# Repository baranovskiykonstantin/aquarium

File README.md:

# DIY Aquarium Controller

## Features
* The controller is based on ATMEL's microcontroller ATMEGA8A
    * Settings are stored in EEPROM
    * Detecting a system hang with Watchdog.
* Remote control via Bluetooth
    * HC-05 module
    * RFCOMM protocol
    * Baud rate 9600 bps
* LED lighting
    * 12V DC output
    * 400mA max.
    * Adjustable brightness
    * Adjustable gradual turning on/off (0-30 min)
    * Adjustable time of turning on/off the light
* Thermostat
    * 220V AC output
    * 3A max. (fused)
    * Adjustable the min. and max. temperature thresholds
* Water temperature measurement
    * DS18B20 sensor
    * Accuracy 0.5 °C
    * Error detecting
* On-board RTC
    * DS1302 chip
    * Adjustable date&time
    * Adjustable daily time correction
    * Backup battery
* 4-digits LED display
    * Two modes of displaying: the current time or the temperature of the water
* Touch control
    * Touch Sensor 1 to switch displaying mode (time -> temperature -> time -> ...)
    * Touch Sensor 1 and Sensor 2 at the same time to switch the operation mode (on -> off -> auto -> on -> ...) of:
        * the lighting if the display shows the time;
        * the heater if the display shows the temperature;
* [Aquarium-control app](https://github.com/baranovskiykonstantin/aquarium-control) is designed to setup the aquarium settings (Windows, Linux, Android, [Symbian](https://github.com/baranovskiykonstantin/AquariumControlS60))

## Wiring diagram

1. Capacitive sensors (aluminum scotch 10x50mm on inner side of the top cover)
2. Mains plug
3. Aquarium controller PCB
4. Power supply PCB
5. Bluetooth module HC-05
6. LEDs (4 x 1W = 12V 300mA)
7. Waterproof DS18B20
8. Heater

## HC-05 configuration
* Change the indicating mode
   * By default LED is blinking on idle and lighting on connecting
   * Disconnect output LED2(31) from PCB's pad that is going to the LED and connect this pad to LED1(32) output
   * Now LED is not lighting on idle and lighting on connecting
* Restore default settings
   * Enter to AT-command mode
   * Send command `AT+ORGL`
* Set device name
   * Enter to AT-command mode
   * Send command `AT+NAME=aquarium` (the device's name must begin with "aquarium" to be recognized by aquarium-control app)
* Reduce power consumption (from ~40mA to ~3mA on idle!)
   * Enter to AT-command mode
   * Send command `AT+IPSCAN=1024,1,1024,1`

## Communicating with the controller
After establishing a connection, you can send commands to the aquarium
controller to setup it.<br>
If a command has the correct format and can be successfully completed the
controller will send OK response. If the command has the wrong format, the
controller will send ERROR response. If the controller receives an unknown
command it will send UNKNOWN response.<br>
The command must end with `\n` or `\r`. If the value of a parameter is bigger
than allowed one it will be reduced to max. allowed value.

### Command `status`
Get information about current state of the aquarium.

Format:

`status`

Response:

```
Date: 01.01.17 Friday
Time: 13:29:59 (-3 sec at 12:00:00)
Temp: 22
Heat: OFF auto (20-22)
Light: ON manual (10:00:00-20:00:00) 43/50% 10min
Display: time
```

Meaning:

Line 1: the current date and the day of the week;<br>
Line 2: the current time and the information about the daily time correction;<br>
Line 3: the temperature of the water (°C);<br>
Line 4: the thermostat status:<br>
* `ON` - the heater is on, `OFF` - the heater is off
* `auto` - automatic mode, `manual` - manual mode
* the value in the parentheses indicates the temperature range that maintains in the automatic mode<br>

Line 5: the lighting status:<br>
* `ON` - the light is on, `OFF` - the light is off
* `auto` - automatic mode, `manual` - manual mode
* the value in the parentheses indicates the period of time when the light is on in the automatic mode<br>
* at the end, the current/target brightness level in percent and the light rising time in minutes

Line 6: the display mode (`time` - the current time is shown, `temp` - the temperature of the water is shown)

### Command `date`
Set a date.

Format:

`date DD.MN.YY W`

Parameters:<br>
* `DD` - day of the month (01-31)
* `MN` - month (01-12)
* `YY` - year (00-99)
* `W` - day of the week (1 - Monday ... 7 - Sunday)

Response:

`OK` or `ERROR`

### Command `time`
Set a time and/or a time correction

Format 1:

`time HH:MM:SS`

Parameters:<br>
* `HH` - hours (00-23)
* `MM` - minutes (00-59)
* `SS` - seconds (00-59)

Format 2:

`time +CC`<br>
`time -CC`

Parameters:<br>
* `+` or `-` - add or subtract the time correction value
* `CC` - time correction in seconds (00-59)

Format 3:

`time HH:MM:SS +CC`<br>
`time HH:MM:SS -CC`

Parameters:<br>
* `HH` - hours (00-23)
* `MM` - minutes (00-59)
* `SS` - seconds (00-59)
* `+` or `-` - add or subtract the time correction value
* `CC` - time correction in seconds (00-59)

Response:

`OK` or `ERROR`

### Command `heat`
Heater setup.

Format 1:

`heat LO-HI`

Parameters:<br>
* `LO` - minimal temperature (18-35)
* `HI` - maximal temperature (18-35)

Format 2:

`heat on`<br>
`heat off`<br>
`heat auto`<br>

Parameters:<br>
* `on` - switch to the manual mode and turn on heater
* `off` - switch to the manual mode and turn off heater
* `auto` - switch to the automatic mode

Response:

`OK` or `ERROR`

### Command `light`
Lighting setup.

Format 1:

`light H1:M1:S1-H2:M2:S2`

Parameters:<br>
* `H1:M1:S1` - light on time (00:00:00-23:59:59)
* `H2:M2:S2` - light off time (00:00:00-23:59:59)

Format 2:

`light on`<br>
`light off`<br>
`light auto`<br>

Parameters:<br>
* `on` - switch to the manual mode and turn on light
* `off` - switch to the manual mode and turn off light
* `auto` - switch to the automatic mode

Format 3:

`light level LLL`

Parameters:<br>
* `LLL` - brightness level in percent (000-100)

Format: 4:

`light rise RR`

Parameters:<br>
* `RR` - time of the light rising in minutes (00-30)

Format: 5:

`light H1:M1:S1-H2:M2:S2 LLL RR`

Parameters:<br>
* `H1:M1:S1` - time of turn on light (00:00:00-23:59:59)
* `H2:M2:S2` - time of turn off light (00:00:00-23:59:59)
* `LLL` - brightness level (000-100)
* `RR` - light rising time (00-30)

Response:

`OK` or `ERROR`

### Command `display`
Display setup.

Format:

`display time`<br>
`display temp`

Parameters:<br>
* `time` - show the current time
* `temp` - show the current temperature of the water

Response:

`OK` or `ERROR`

### Command `reboot`
Restart the program.

Format:

`reboot`

Response:

`OK`

### Command `help`
Print the list of available commands.

Format:

`help`

Response:

```
Available commands:

status
date DD.MN.YY W
time HH:MM:SS
time +CC
time -CC
time HH:MM:SS +CC
time HH:MM:SS -CC
heat LO-HI
heat on
heat off
heat auto
light H1:M1:S1-H2:M2:S2
light level LLL
light rise RR
light H1:M1:S1-H2:M2:S2 LLL RR
light on
light off
light auto
display time
display temp
reboot
help

```

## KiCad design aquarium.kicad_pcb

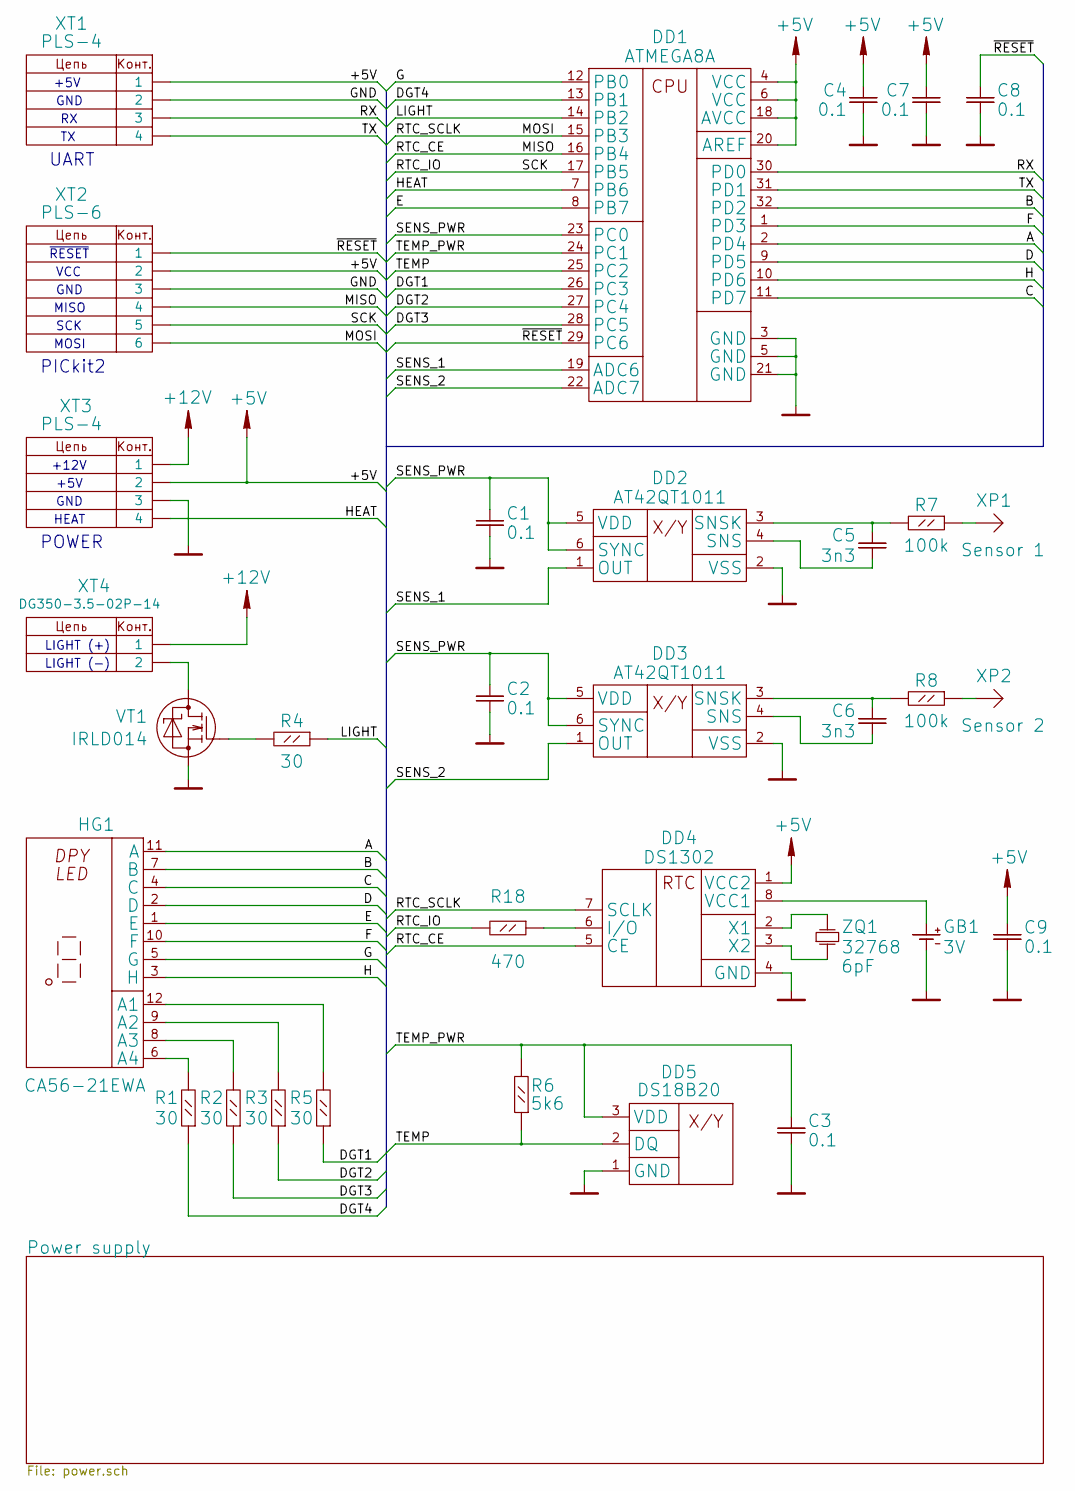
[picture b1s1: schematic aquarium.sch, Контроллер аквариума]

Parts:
C1, C2, C3, C4, C7, C8, C9: 0.1; SMD_0805
C5, C6: 3n3; SMD_0805
DD1: ATMEGA8A; TQFP32-30
DD2, DD3: AT42QT1011; SOT23-6
DD4: DS1302; DIP8-300
DD5: DS18B20; PLS-3
GB1: 3V; CR2032_H
HG1: CA56-21EWA; 56-21_smd
R1, R2, R3, R4, R5: 30; R_0805
R6: 5k6; R_0805
R7, R8: 100k; R_0805
R18: 470; R_0805
VT1: IRLD014; HVMDIP
XP1: Sensor 1; PLS-1
XP2: Sensor 2; PLS-1
XT1, XT3: PLS-4
XT2: PLS-6
XT4: DG350-3.5-02P-14; DG-350-2
ZQ1: 32768; HC_3.0x8.0mm

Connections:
+5V: C4.1, C7.1, C9.1, DD1.4 (VCC), DD1.6 (VCC), DD1.18 (AVCC), DD1.20 (AREF), DD4.1 (VCC2), XT1.1, XT2.2, XT3.2; also elsewhere on the board
+12V: XT3.1, XT4.1; also elsewhere on the board
/A: DD1.2 (PD4), HG1.11 (A)
/B: DD1.32 (PD2), HG1.7 (B)
/C: DD1.11 (PD7), HG1.4 (C)
/D: DD1.9 (PD5), HG1.2 (D)
/DGT1: DD1.26 (PC3), R5.1
/DGT2: DD1.27 (PC4), R3.1
/DGT3: DD1.28 (PC5), R2.1
/DGT4: DD1.13 (PB1), R1.1
/E: DD1.8 (PB7), HG1.1 (E)
/F: DD1.1 (PD3), HG1.10 (F)
/G: DD1.12 (PB0), HG1.5 (G)
/H: DD1.10 (PD6), HG1.3 (H)
/HEAT: DD1.7 (PB6), XT3.4
/LIGHT: DD1.14 (PB2), R4.1
/MISO: DD1.16 (PB4), DD4.5 (CE), XT2.4
/MOSI: DD1.15 (PB3), DD4.7 (SCLK), XT2.6
/RTC_IO: DD1.17 (PB5), R18.2, XT2.5
/RX: DD1.30 (PD0), XT1.3
/SENS_1: DD1.19 (ADC6), DD2.1 (OUT)
/SENS_2: DD1.22 (ADC7), DD3.1 (OUT)
/SENS_PWR: C1.1, C2.1, DD1.23 (PC0), DD2.5 (VDD), DD2.6 (SYNC), DD3.5 (VDD), DD3.6 (SYNC)
/TEMP: DD1.25 (PC2), DD5.2 (DQ), R6.1
/TEMP_PWR: C3.1, DD1.24 (PC1), DD5.3 (VDD), R6.2
/TX: DD1.31 (PD1), XT1.4
/~RESET: C8.1, DD1.29 (PC6), XT2.1
GND: C1.2, C2.2, C3.2, C4.2, C7.2, C8.2, C9.2, DD1.3 (GND), DD1.5 (GND), DD1.21 (GND), DD2.2 (VSS), DD3.2 (VSS), DD4.4 (GND), DD5.1 (GND), GB1.2 (-), VT1.3 (S), XT1.2, XT2.3, XT3.3; also elsewhere on the board
unnamed: C5.1, DD2.3 (SNSK), R7.2
unnamed: C5.2, DD2.4 (SNS)
unnamed: C6.1, DD3.3 (SNSK), R8.2
unnamed: C6.2, DD3.4 (SNS)
unnamed: DD4.2 (X1), ZQ1.2
unnamed: DD4.3 (X2), ZQ1.1
unnamed: DD4.6 (I/O), R18.1
unnamed: DD4.8 (VCC1), GB1.1 (+)
unnamed: HG1.6 (A4), R1.2
unnamed: HG1.8 (A3), R2.2
unnamed: HG1.9 (A2), R3.2
unnamed: HG1.12 (A1), R5.2
unnamed: R4.2, VT1.2 (G)
unnamed: R7.1, XP1.1
unnamed: R8.1, XP2.1
unnamed: VT1.1 (D), XT4.2

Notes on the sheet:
LIGHT (+)
LIGHT (-)
+5V
GND
UART
PICkit2
MISO
VCC
SCK
MOSI
~RESET
HEAT
+12V
POWER

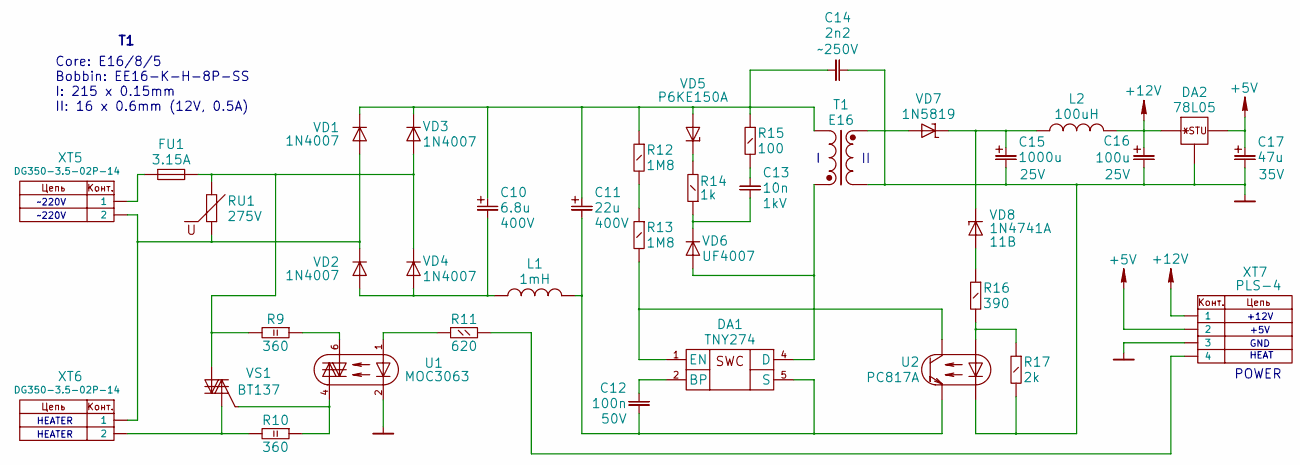
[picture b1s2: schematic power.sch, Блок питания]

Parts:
C10: 6.8u; CPH_5_10x16mm
C11: 22u; CPH_5_13x25mm
C12: 100n; C_5x3mm
C13: 10n; C_5x3mm
C14: 2n2; C_7.5x4mm
C15: 1000u; CPH_5_10x20mm
C16: 100u; CP_2.5x6mm
C17: 47u; CP_2.5x5mm
DA1: TNY274; PDIP-8C
DA2: 78L05; TO92-250
FU1: 3.15A; FU_5x20mm
L1: 1mH; Ind_5x8mm
L2: 100uH; Ind_5x8mm
R9, R10: 360; RH_2
R11: 620; RH_0.25
R12, R13: 1M8; RV_0.25
R14: 1k; RV_0.25
R15: 100; RV_0.25
R16: 390; RV_0.25
R17: 2k; RV_0.25
RU1: 275V; FNR-05
T1: E16; E16_5_10mm
U1: MOC3063; DIP6-300
U2: PC817A; DIP4-300
VD1, VD2, VD3, VD4: 1N4007; DO-41
VD5: P6KE150A; DO-15
VD6: UF4007; DO-41
VD7: 1N5819; DO-41
VD8: 1N4741A; DO-41
VS1: BT137; TO220
XT5, XT6: DG350-3.5-02P-14; DG-350-2
XT7: PLS-4

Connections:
+5V: C17.1, DA2.1 (OUT), XT7.2; also elsewhere on the board
+12V: C16.1, DA2.3 (IN), L2.2, XT7.1; also elsewhere on the board
GND: C14.1, C15.2, C16.2, C17.2, DA2.2 (GND), R17.2, T1.4 (S2), U1.2 (K), U2.2 (K), XT7.3; also elsewhere on the board
unnamed: C10.1, C11.1, C14.2, R12.1, R15.1, T1.2, VD1.2 (K), VD3.2 (K), VD5.1 (A)
unnamed: C10.2, L1.1, VD2.1 (A), VD4.1 (A)
unnamed: C11.2, C12.2, DA1.5 (S), L1.2, U2.3 (E)
unnamed: C12.1, DA1.2 (BP)
unnamed: C13.1, R15.2
unnamed: C13.2, R14.1, VD6.2 (K)
unnamed: C15.1, L2.1, VD7.2 (K), VD8.2 (K)
unnamed: DA1.1 (EN), R13.2, U2.4 (C)
unnamed: DA1.4 (D), T1.1, VD6.1 (A)
unnamed: FU1.1, XT5.1
unnamed: FU1.2, R9.2, RU1.2, VD3.1 (A), VD4.2 (K), VS1.2
unnamed: R9.1, U1.6 (MT)
unnamed: R10.1, U1.4 (MT), VS1.3 (G)
unnamed: R10.2, VS1.1, XT6.2
unnamed: R11.1, U1.1 (A)
unnamed: R11.2, XT7.4
unnamed: R12.2, R13.1
unnamed: R14.2, VD5.2 (K)
unnamed: R16.1, VD8.1 (A)
unnamed: R16.2, R17.1, U2.1 (A)
unnamed: RU1.1, VD1.1 (A), VD2.2 (K), XT5.2, XT6.1
unnamed: T1.3 (S1), VD7.1 (A)

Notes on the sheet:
~~220V
HEATER
+5V
HEAT
+12V
GND
POWER
Core: E16/8/5 Bobbin: EE16-K-H-8P-SS I: 215 x 0.15mm II: 16 x 0.6mm (12V, 0.5A)

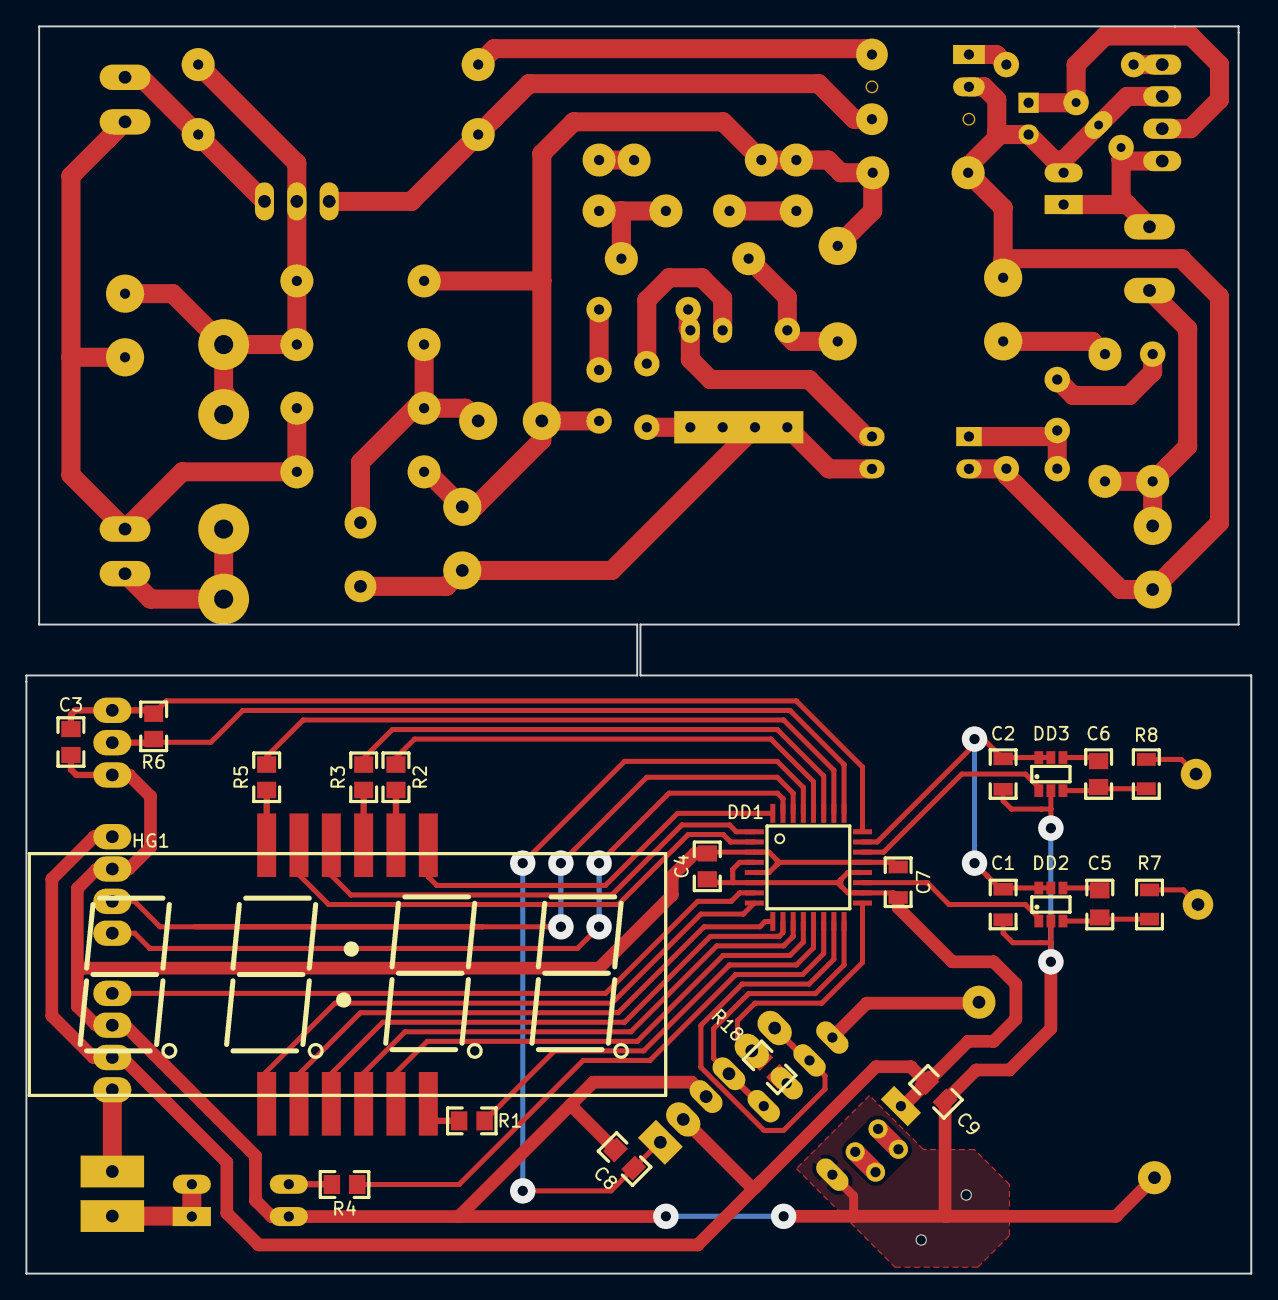
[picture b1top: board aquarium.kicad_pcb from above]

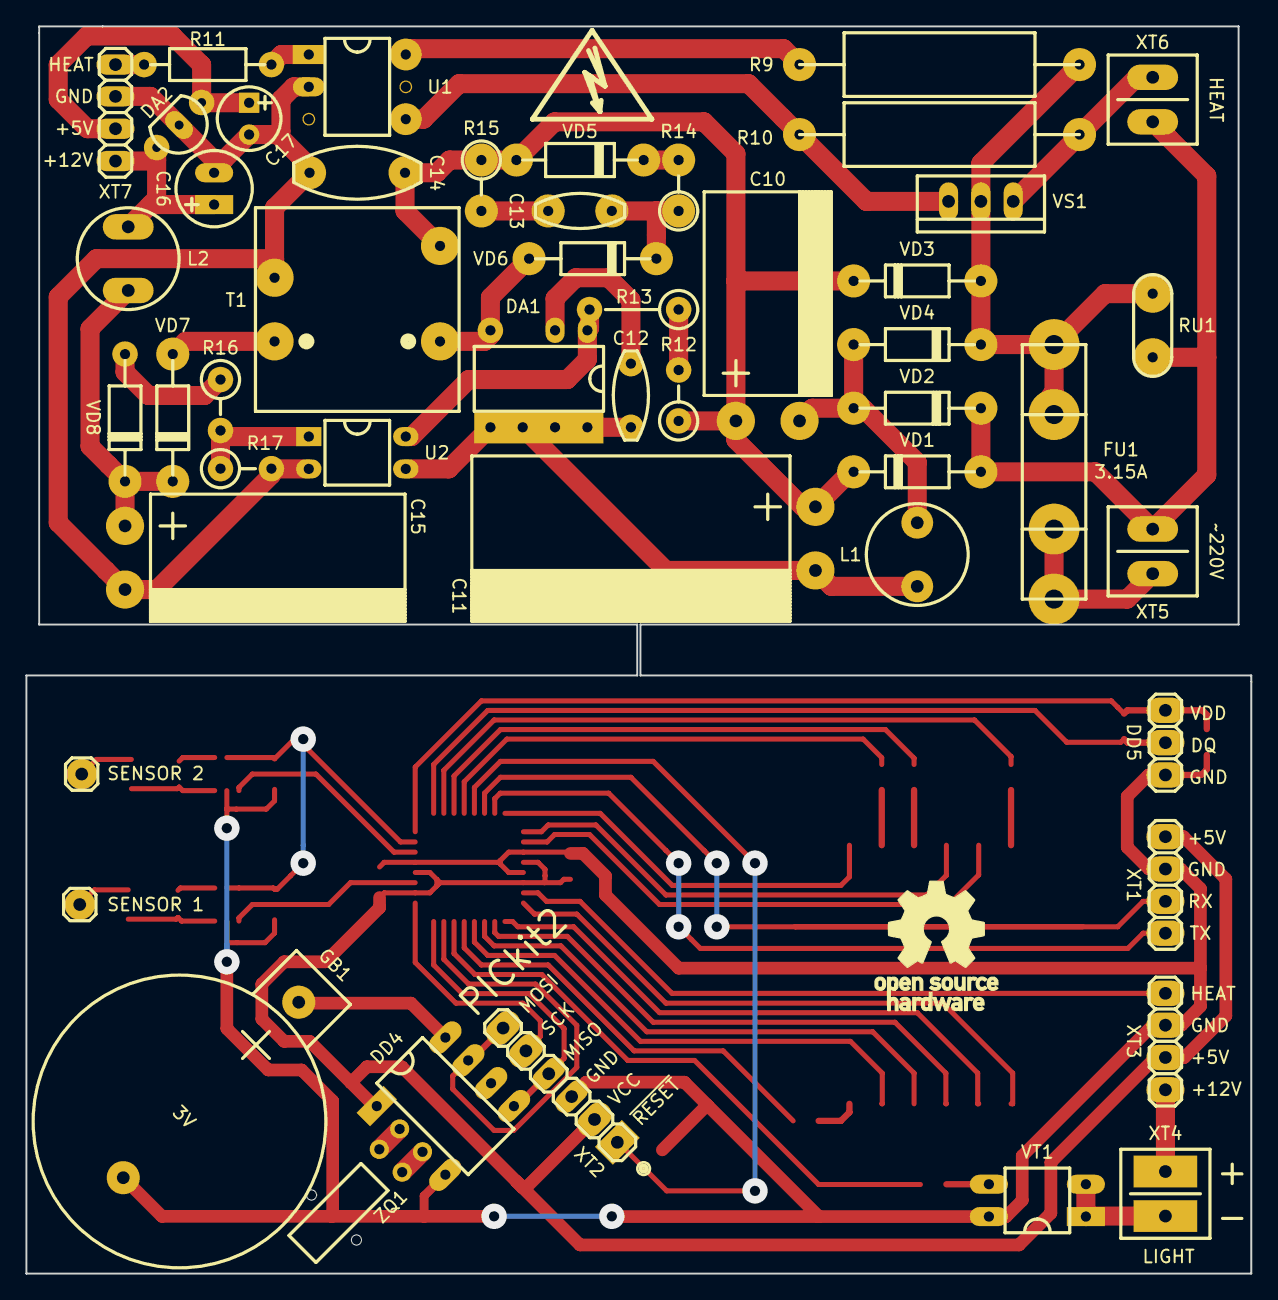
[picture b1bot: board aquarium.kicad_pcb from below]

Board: 2 copper layers, 96.2 x 98.0 mm, 71 parts (49 on the bottom side), 66 nets.

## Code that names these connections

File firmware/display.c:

/* Name: display.c
 * Project: aquarium
 * Author: Baranovskiy Konstantin
 * Creation Date: 2015-12-28
 * Tabsize: 4
 * Copyright: (c) 2017-2019 Baranovskiy Konstantin
 * License: GNU GPL v3 (see License.txt)
 */

#include <avr/interrupt.h>
#include <stdlib.h>

#include "display.h"
#include "ds18b20.h"

#define MSG_DELAY 3906 // 3906 * 256us (T2_OVF) = 1 sec

static volatile uint8_t display[4];
static volatile uint8_t current_digit;
static volatile uint8_t current_segment;
static volatile uint16_t message_delay;

typedef struct
{
    volatile uint8_t *port;
    uint8_t pin;
} pin_t;

static const pin_t digits[4] = {
    {&PORTB, PB1}, // 1
    {&PORTC, PC5}, // 2
    {&PORTC, PC4}, // 3
    {&PORTC, PC3}  // 4
};

static const pin_t segments[8] = {
    {&PORTD, PD4}, // A
    {&PORTD, PD2}, // B
    {&PORTD, PD7}, // C
    {&PORTD, PD5}, // D
    {&PORTB, PB7}, // E
    {&PORTD, PD3}, // F
    {&PORTB, PB0}, // G
    {&PORTD, PD6}  // H
};

static const uint8_t symbols[] = {
    //HGFEDCBA
    0b00111111,   // 0  - 0      --A--
    0b00000110,   // 1  - 1    |       |
    0b01011011,   // 2  - 2    F       B
    0b01001111,   // 3  - 3    |       |
    0b01100110,   // 4  - 4     ---G---
    0b01101101,   // 5  - 5    |       |
    0b01111101,   // 6  - 6    E       C
    0b00000111,   // 7  - 7    |       |
    0b01111111,   // 8  - 8      --D--  _H
    0b01101111    // 9  - 9
};
//  0b00111111       O  - 0x3F
//  0b01010100       n  - 0x54
//  0b01110001       F  - 0x71
//  0b01110111       A  - 0x77
//  0b00111110       U  - 0x3E
//  0b01111000       t  - 0x78
//  0b01000000       -  - 0x40

void display_init(void)
{
    // I/O ports
    PORTB |= 0x83;
    DDRB |= 0x83;
    PORTC |= 0x38;
    DDRC |= 0x38;
    PORTD |= 0xFC;
    DDRD |= 0xFC;

    // Timer 2 - switch segments on display dynamically every 256 us
    TCCR2 |= (1 << CS21); // Normal mode, clk/8
    TCNT2 = 0x00; // 256 us
    TIMSK |= (1 << TOIE2); // Enable overflow on timer 2

    // Variables
    current_digit = 0;
    current_segment = 0;
    display[0] = 0xff;
    display[1] = 0xff;
    display[2] = 0xff;
    display[3] = 0xff;
}

void display_time(time_t *time)
{
    if (message_delay > 0)
    {
        return;
    }

    display[0] = symbols[time->min % 10];
    display[1] = symbols[time->min / 10];
    display[2] = symbols[time->hour % 10];
    display[3] = (time->hour < 10) ? 0x00 : symbols[time->hour / 10];
    // Colon at even seconds
    if (!(time->sec % 2))
    {
        display[0] |= 0x80;
        display[1] |= 0x80;
    }
}

void display_temp(int8_t temp)
{
    if (message_delay > 0)
    {
        return;
    }

    if (temp == DS18B20_ERR)
    {
        // " -- "
        display[0] = 0x00;
        display[1] = 0x40;
        display[2] = 0x40;
        display[3] = 0x00;
    }
    else if (labs(temp) < 10)
    {
        display[0] = 0x00;
        display[1] = symbols[labs(temp)];
        display[2] = (temp < 0) ? 0x40 : 0x00;
        display[3] = 0x00;
    }
    else if (labs(temp) < 100)
    {
        display[0] = 0x00;
        display[1] = symbols[labs(temp) % 10];
        display[2] = symbols[labs(temp) / 10];
        display[3] = (temp < 0) ? 0x40 : 0x00;
    }
    else
    {
        display[0] = symbols[labs(temp) % 10];
        display[1] = symbols[labs(temp) % 100 / 10];
        display[2] = symbols[labs(temp) % 1000 / 100];
        display[3] = 0x00;
    }
}

void display_message_on(void)
{
    display[0] = 0x00;
    display[1] = 0x54;
    display[2] = 0x3f;
    display[3] = 0x00;
    message_delay = MSG_DELAY;
}

void display_message_off(void)
{
    display[0] = 0x71;
    display[1] = 0x71;
    display[2] = 0x3f;
    display[3] = 0x00;
    message_delay = MSG_DELAY;
}

void display_message_auto(void)
{
    display[0] = 0x3f;
    display[1] = 0x78;
    display[2] = 0x3E;
    display[3] = 0x77;
    message_delay = MSG_DELAY;
}

ISR (TIMER2_OVF_vect)
{
    uint8_t i;

    // Turn off all digits
    for (i = 0; i < 4; i++)
    {
        *(digits[i].port) &= ~(1 << digits[i].pin);
    }

    // Turn off all segments
    for (i = 0; i < 8; i++)
    {
        *(segments[i].port) |= (1 << segments[i].pin);
    }

    // Turn on current segment if needed
    if (display[current_digit] & (1 << current_segment))
    {
        *(segments[current_segment].port) &= ~(1 << segments[current_segment].pin);
    }

    // Turn on current digit
    *(digits[current_digit].port) |= (1 << digits[current_digit].pin);

    if (++current_segment > 7)
    {
        current_segment = 0;
        if (++current_digit > 3)
        {
            current_digit = 0;
        } // All digits 0..3
    } // All segments 0..7

    if (message_delay > 0)
    {
        message_delay -= 1;
    }
}

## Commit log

2016-01-18 Initial commit.
2016-01-18 ATmega48PA changet to ATmega8A
2016-01-18 Added noise filtering to sensor input.
2016-01-24 Added some comments.
2016-01-27 Added possibility to calibrate the capacitive sensor.
2016-01-27 Update README.md.
2016-02-04 Revert "Added possibility to calibrate the capacitive sensor."
    This reverts commit 56735a840efcf7c901892eb1b50b215983c0ef84.
2016-02-08 Corrected sensitivity of the sensor and added noise protection on Reset pin.
2016-02-18 Small correction of the comments.
2016-02-21 Added daily time correction and more UART commands.
2016-02-22 Changed capacity of the reference capacitor of the sensor IC. Corrected initialization of the time correction variable.
2016-03-24 Preventing EEPROM corruption on power off.
2016-03-24 Updated README.md and schematic image.
2016-05-15 Add photo of the aquarium.
2016-12-05 * Renamed command ''state'' to ''status''. * Enabled watchdog timer. * Optimized work with DS18B20.
2017-01-05 Firmware: remove delay from main loop.
2017-01-05 Added new file of worksheet frame.
2017-01-16 New version of the controller (schematic and pcb).
2017-01-30 Small changes to PCB.
2017-02-05 Finished working on PCB.
2017-03-11 Udated firmware for new version of the schematic.
2017-03-11 New version of the schematic and PCB's.
2017-03-11 Update images.
2017-03-12 Remove optional capacitor from schematic.
2017-04-16 Firmware updates: * fixed time correction; * changed main loop processing; * added sensor signal filtering.
2017-06-05 Added some new commands.
2017-06-05 Fix typo in README.md.
2017-07-23 Fix time correction.
2017-11-01 README totally reworked.
2017-11-03 Fix temp sersor errors counting.
2017-12-11 Added new feature: light rise time adjusting.
2018-01-05 Code refactoring.
2019-09-06 Complete code restructuring.
2019-09-22 Note about BT-device naming was added.
2019-09-24 Schematic/PCB update to the latest KiCad.
2021-03-18 Fix year format in status response.
2021-03-21 Add the mention about Symbian OS to app description.
